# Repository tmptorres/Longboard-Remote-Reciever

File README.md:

# Longboard-Remote-Reciever

A reciever board that uses an Arduino Nano and a 2.4GHz nRF24 WiFi module.
Has two dedicated outputs for PWM servo connections or boards recieving the signals.
5V power can be provided by either the PWM connections OR 3.3V power can be provided by the side connector.

## Product

## Top View

## Bottom View

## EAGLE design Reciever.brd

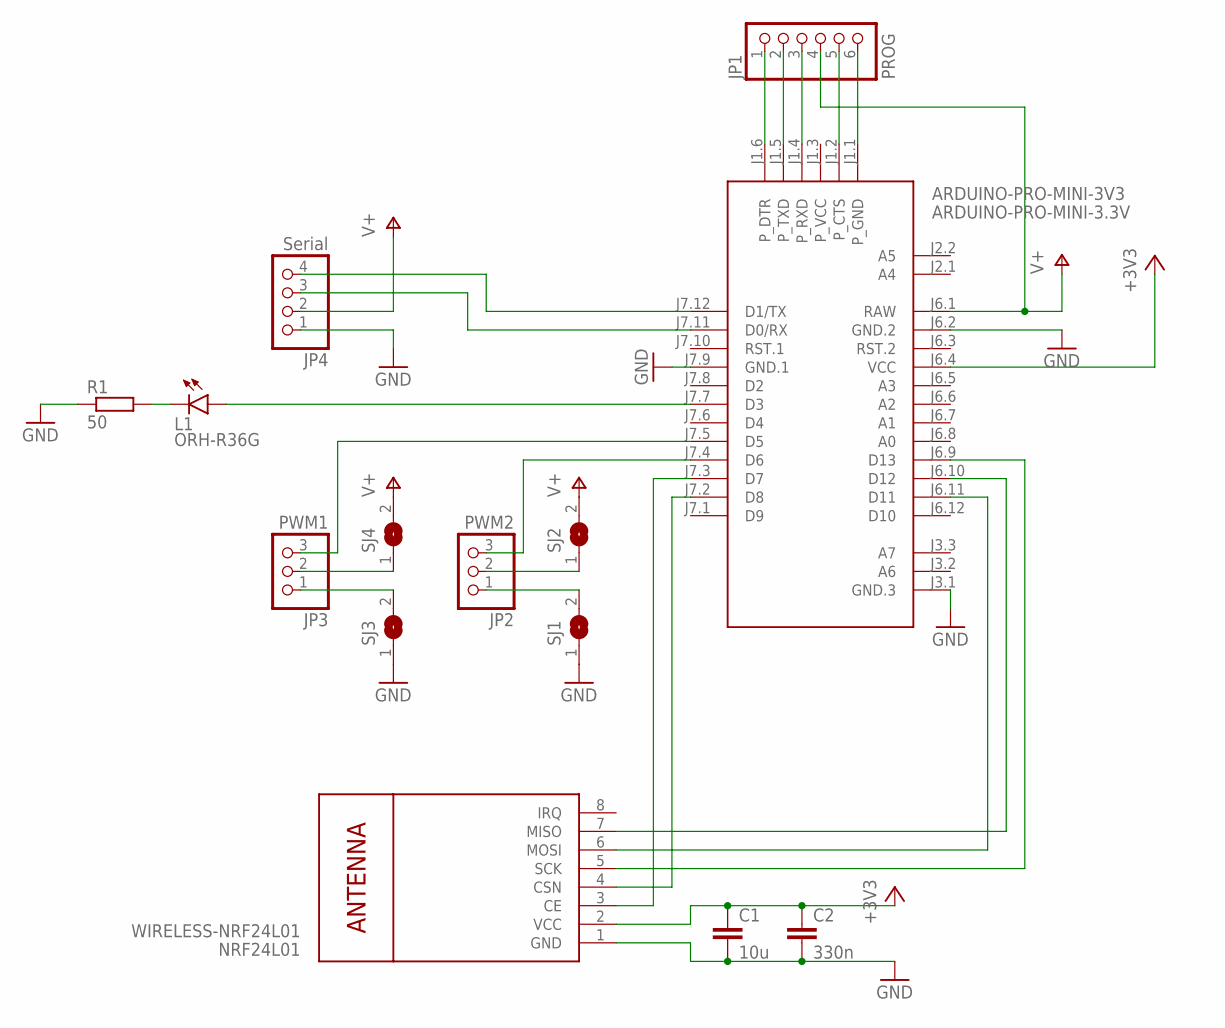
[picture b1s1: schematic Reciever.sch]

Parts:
ARDUINO-PRO-MINI-3V3: ARDUINO-PRO-MINI-3.3V; ARDUINO-PRO-MINI
C1: 10u; C0805
C2: 330n; C0805
JP1: PROG; 1X06
JP2: PWM2; 1X03/90
JP3: PWM1; 1X03/90
JP4: Serial; 1X04
L1: ORH-R36G; CHIP-LED0603
NRF24L01: WIRELESS-NRF24L01
R1: 50; R0603
SJ1, SJ2, SJ3, SJ4: SJW

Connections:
+3V3: ARDUINO-PRO-MINI-3V3.J6.4 (VCC), C1.1, C2.1, NRF24L01.2 (VCC)
GND: ARDUINO-PRO-MINI-3V3.J3.1 (GND.3), ARDUINO-PRO-MINI-3V3.J6.2 (GND.2), ARDUINO-PRO-MINI-3V3.J7.9 (GND.1), C1.2, C2.2, JP4.1, NRF24L01.1 (GND), R1.1, SJ1.1, SJ3.1
unnamed: ARDUINO-PRO-MINI-3V3.J7.7 (D3), L1.A
unnamed: JP2.1, SJ1.2
unnamed: ARDUINO-PRO-MINI-3V3.J7.5 (D5), JP3.3
unnamed: ARDUINO-PRO-MINI-3V3.J7.3 (D7), NRF24L01.3 (CE)
unnamed: ARDUINO-PRO-MINI-3V3.J7.2 (D8), NRF24L01.4 (CSN)
unnamed: ARDUINO-PRO-MINI-3V3.J6.9 (D13), NRF24L01.5 (SCK)
unnamed: ARDUINO-PRO-MINI-3V3.J6.11 (D11), NRF24L01.6 (MOSI)
unnamed: ARDUINO-PRO-MINI-3V3.J6.10 (D12), NRF24L01.7 (MISO)
unnamed: JP2.2, SJ2.1
unnamed: ARDUINO-PRO-MINI-3V3.J7.4 (D6), JP2.3
unnamed: JP3.1, SJ3.2
unnamed: JP3.2, SJ4.1
unnamed: ARDUINO-PRO-MINI-3V3.J7.12 (D1/TX), JP4.4
unnamed: ARDUINO-PRO-MINI-3V3.J7.11 (D0/RX), JP4.3
unnamed: L1.C, R1.2
unnamed: ARDUINO-PRO-MINI-3V3.J1.6 (P_DTR), JP1.1
unnamed: ARDUINO-PRO-MINI-3V3.J1.5 (P_TXD), JP1.2
unnamed: ARDUINO-PRO-MINI-3V3.J1.4 (P_RXD), JP1.3
unnamed: ARDUINO-PRO-MINI-3V3.J1.2 (P_CTS), JP1.5
unnamed: ARDUINO-PRO-MINI-3V3.J1.1 (P_GND), JP1.6
V+: ARDUINO-PRO-MINI-3V3.J6.1 (RAW), JP1.4, JP4.2, SJ2.2, SJ4.2

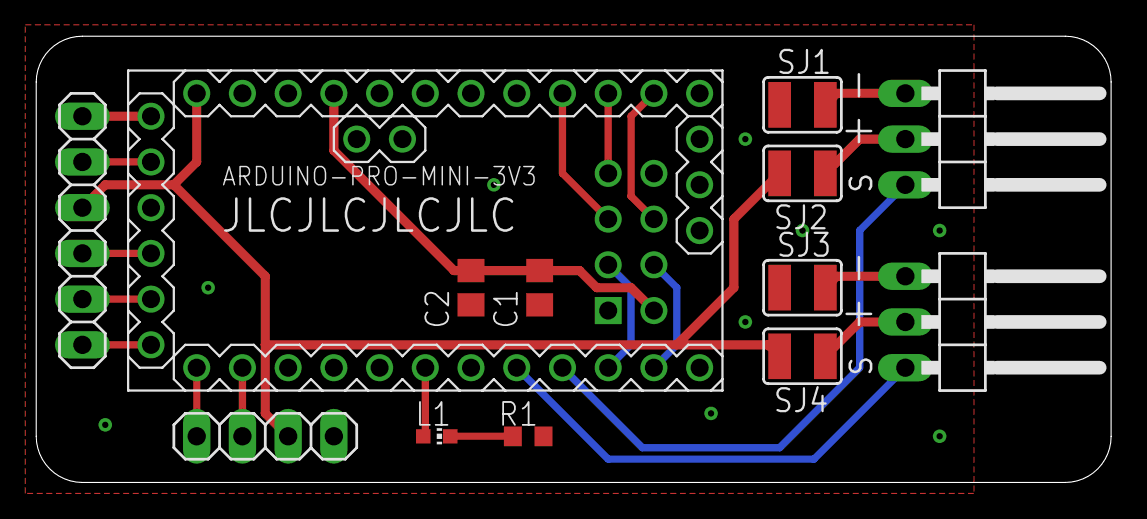
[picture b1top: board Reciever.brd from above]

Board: 2 copper layers, 59.7 x 24.8 mm, 14 parts (1 on the bottom side), 23 nets.

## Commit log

2019-08-11 Initial commit with remote design & CAM file used for production.
2019-08-11 Added board images and updated readme
2019-08-11 Fixing images in readme
2019-08-11 Updated board images with visible ground planes
2021-01-18 Updated the Readme.md file and added a product image
2021-01-18 Added license

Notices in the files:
parts and their libraries:
diy-modules: Released under the Creative Commons Attribution 4.0 International License: http://creativecommons.org/licenses/by/4.0
